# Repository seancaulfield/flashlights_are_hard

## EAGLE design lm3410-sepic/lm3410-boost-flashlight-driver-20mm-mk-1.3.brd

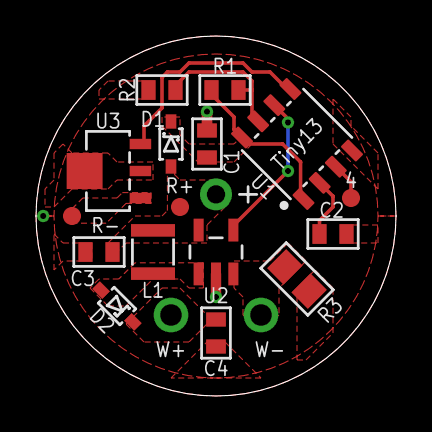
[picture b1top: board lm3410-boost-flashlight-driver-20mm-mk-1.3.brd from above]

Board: 2 copper layers, 20.0 x 20.0 mm, 21 parts (1 on the bottom side), 12 nets.

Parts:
4: M01SMD-1MM-DIA-NS; 1X01-SMD-1MM-DIA-NS
+: M01PTH-1MM-CIR-NS; 1X01-1MM-CIR-NS
-: M01NOT-A-VIA-NOPE; 1X01_NOSILK_NOSTOP
C1, C4: 10u; C0603-TIGHTER
C2: 1u; C0603-TIGHTER
C3: 4u7; C0603-TIGHTER
D1, D2: BAT165; SOD323-SCHOTTKY
FRAME1: FRAME-LETTERNO_PACKAGE; DUMMY
L1: 1uH; PFL2512
R1: 19K; R0603-TIGHTER
R2: 4K7; R0603-TIGHTER
R3: 0R127; R0805
R+: M01SMD-1MM-DIA-NS; 1X01-SMD-1MM-DIA-NS
R-: M01SMD-1MM-DIA-NS; 1X01-SMD-1MM-DIA-NS
U1: Tiny13; SO08-NARROWER
U2: LM3410XMF; SOT95P285X120-5N
U3: '7135; SOT89-NOTHERM
W+: M01PTH-1.2MM-NS; 1X01-1.2MM-NS
W-: M01PTH-1.2MM-NS; 1X01-1.2MM-NS

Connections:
4: 4.P$1, U1.3
GND: -.P$1, C1.2, C2.2, C3.2, C4.2, R2.1, R3.1, U1.4, U2.2, U3.4@1, U3.4@2
unnamed: C2.1, U1.2
PWM1: U1.6, U2.4
PWM2: U1.5, U3.3
R-: R-.P$1, U3.1
SW: D2.A, L1.P$2, U2.1
VBAT: +.1, C3.1, D1.A, L1.P$1, R+.P$1, U2.5
VCC: C1.1, D1.C, R1.2, U1.1, U1.8
VDIV: R1.1, R2.2, U1.7
WHITE+: C4.1, D2.C, W+.P$1
WHITE-: R3.2, U2.3, W-.P$1

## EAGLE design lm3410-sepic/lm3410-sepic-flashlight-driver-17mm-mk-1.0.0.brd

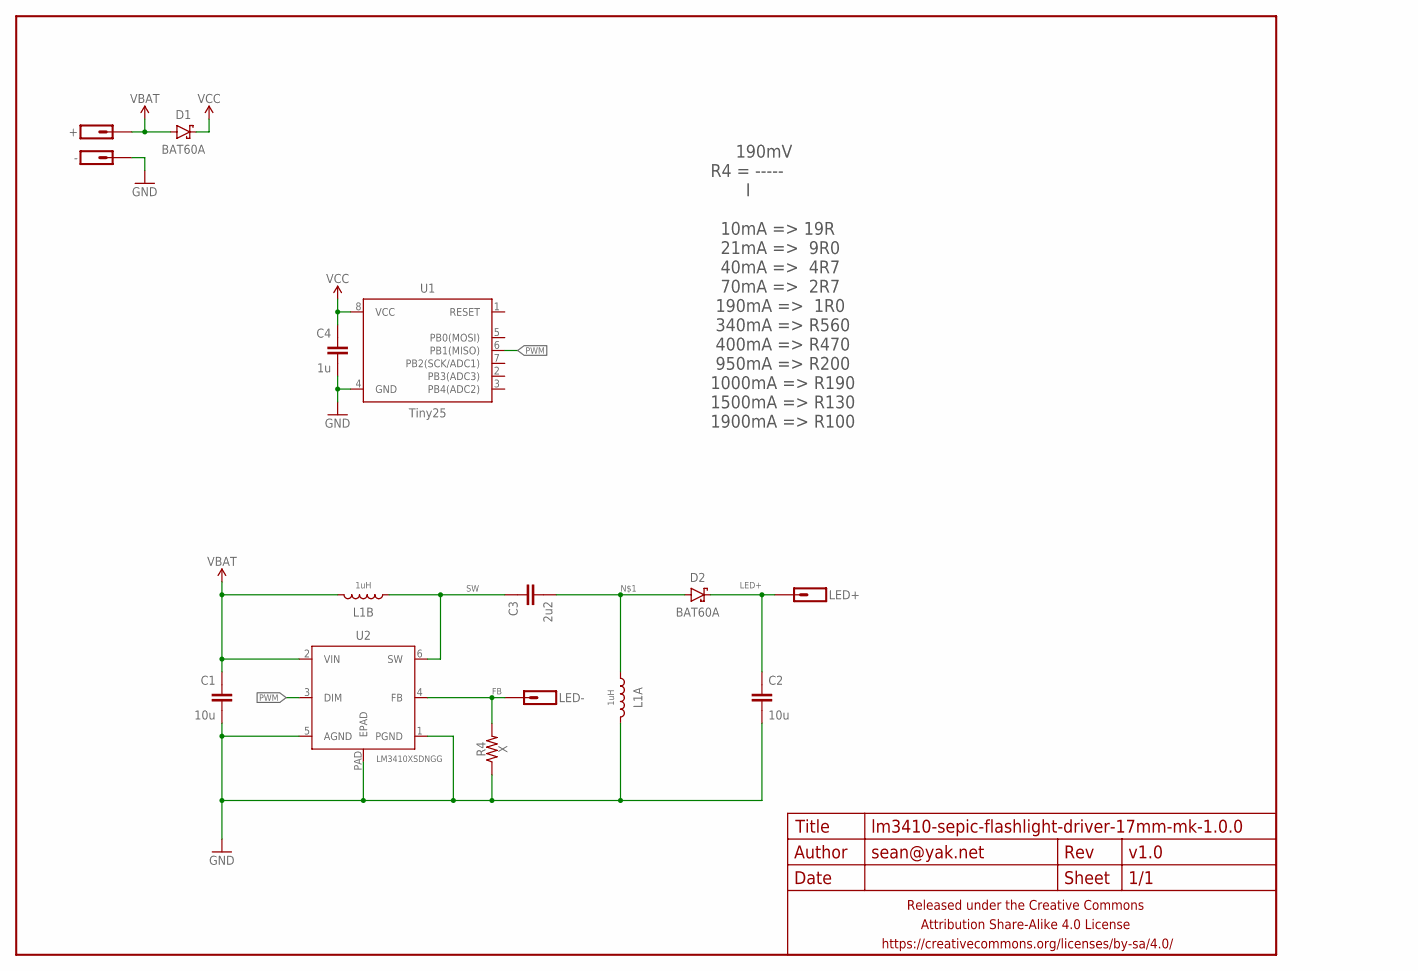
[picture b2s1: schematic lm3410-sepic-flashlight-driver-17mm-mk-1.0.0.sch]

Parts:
+: M01NOT-A-VIA-NOPE; 1X01_NOSILK_NOSTOP
-: M01NOT-A-VIA-NOPE; 1X01_NOSILK_NOSTOP
C1, C2: 10u; C0805-TIGHTER
C3: 2u2; C0603-TIGHTER
C4: 1u; C0603-TIGHTER
D1, D2: BAT60A; SOD323-SCHOTTKY
FRAME1: FRAME-LETTERNO_PACKAGE; DUMMY
L1: 1uH; LPD5030
LED+: M01PTH-1MM-CIR-NS; 1X01-1MM-CIR-NS
LED-: M01PTH-1MM-CIR-NS; 1X01-1MM-CIR-NS
R4: X; R0805-TIGHTER
U1: Tiny25; SO08-SKINNYPADS
U2: LM3410XSDNGG; DFN300X300X80-7N

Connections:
FB: LED-.1, R4.2, U2.4 (FB)
GND: -.P$1, C1.2, C2.2, C4.2, L1.2, R4.1, U1.4 (GND), U2.1 (PGND), U2.5 (AGND), U2.PAD (EPAD)
LED+: C2.1, D2.C, LED+.1
unnamed: C3.2, D2.A, L1.1
PWM: U1.6 (PB1(MISO)), U2.3 (DIM)
SW: C3.1, L1.4 (1), U2.6 (SW)
VBAT: +.P$1, C1.1, D1.A, L1.3 (2), U2.2 (VIN)
VCC: C4.1, D1.C, U1.8 (VCC)

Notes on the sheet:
190mV R4 = ----- I 10mA => 19R 21mA => 9R0 40mA => 4R7 70mA => 2R7 190mA => 1R0 340mA => R560 400mA => R470 950mA => R200 1000mA => R190 1500mA => R130 1900mA => R100

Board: 2 copper layers, 15 parts (1 on the bottom side), 8 nets, no tracks yet.

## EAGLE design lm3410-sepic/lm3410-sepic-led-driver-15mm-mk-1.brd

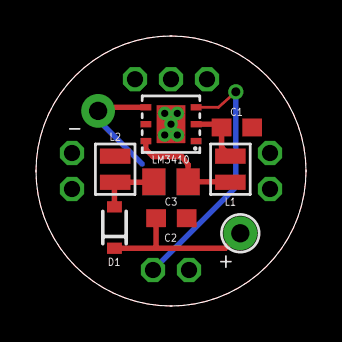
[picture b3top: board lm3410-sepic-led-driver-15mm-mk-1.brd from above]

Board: 2 copper layers, 15.0 x 15.0 mm, 14 parts (1 on the bottom side), 7 nets.

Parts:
+: M01PTH-KIT; 1X01-KIT
-: M01NOSILK-KIT; 1X01NS-KIT
C1, C2: 10uF; C0603
C3: 2.2uF; C0805
D1: BAT20J; SOD-323
JP1: 1X03-2MM-PTH
JP2, JP3, JP4: M02PTH-2MM; 1X02-2MM-PTH
L1, L2: 4.7uH; INDUCTOR_2X1.6MM
LM3410: LM3410XSD; DFN300X300X80-7N
R1: 0.68; R1206

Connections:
D0: JP3.P$1, LM3410.3
GND: C1.2, C2.2, JP1.P$1, JP1.P$3, L2.P$2, LM3410.1, LM3410.5, LM3410.7, LM3410.7@1, LM3410.7@2, LM3410.7@3, LM3410.7@4, LM3410.7@5, R1.1
LED_ANODE: +.1, C2.1, D1.C
unnamed: C3.2, D1.A, L2.P$1
unnamed: -.1, LM3410.4, R1.2
SW: C3.1, L1.P$2, LM3410.6
V_BATT+: C1.1, JP1.P$2, L1.P$1, LM3410.2

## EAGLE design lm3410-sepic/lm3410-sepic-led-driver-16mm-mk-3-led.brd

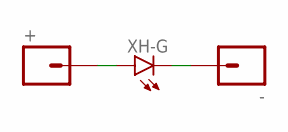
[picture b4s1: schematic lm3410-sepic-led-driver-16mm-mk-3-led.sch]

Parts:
+: M01PTH-1.2MM; 1X01-1.2MM
-: M01PTH-1.2MM-NS; 1X01-1.2MM-NS
XH-G: LEDBIG-ASS-RED-LED; LED-GULL-WINGS-MINE-MINE-MINE

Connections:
GND: -.P$1, XH-G.K (C), XH-G.K@1 (C), XH-G.K@3 (C), XH-G.K@4 (C), XH-G.K@5 (C), XH-G.K@7 (C), XH-G.K@8 (C), XH-G.K@9 (C), XH-G.K@10 (C), XH-G.K@11 (C), XH-G.K@12 (C), XH-G.K@13 (C), XH-G.K@14 (C), XH-G.K@15 (C), XH-G.K@16 (C), XH-G.K@17 (C), XH-G.K@18 (C), XH-G.K@19 (C), XH-G.K@20 (C), XH-G.K@21 (C), XH-G.K@23 (C), XH-G.K@24 (C), XH-G.K@25 (C)
VCC: +.P$1, XH-G.A

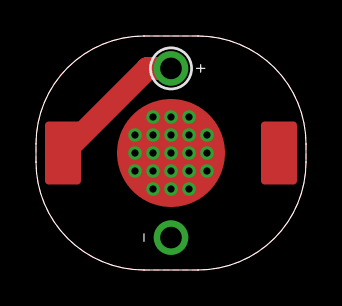
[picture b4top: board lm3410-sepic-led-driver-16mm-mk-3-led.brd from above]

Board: 2 copper layers, 15.0 x 13.0 mm, 3 parts (0 on the bottom side), 2 nets.

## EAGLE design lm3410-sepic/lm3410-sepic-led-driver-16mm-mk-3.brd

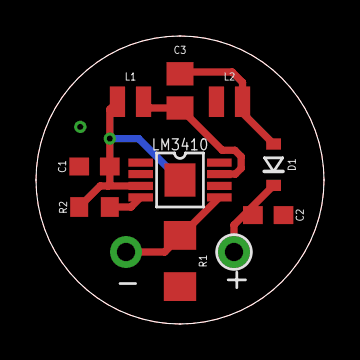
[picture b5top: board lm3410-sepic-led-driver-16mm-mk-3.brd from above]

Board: 2 copper layers, 16.0 x 16.0 mm, 13 parts (0 on the bottom side), 7 nets.

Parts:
+: M01PTH-KIT; 1X01-KIT
-: M01NOSILK-KIT; 1X01NS-KIT
C1, C2: 10uF; C0603
C3: 2.2uF; C0805
D1: BAT20J; SOD-323
JBATT+: M01NOT-A-VIA-NOPE; 1X01_NOSILK_NOSTOP
JBATT-: M01NOT-A-VIA-NOPE; 1X01_NOSILK_NOSTOP
L1, L2: 4.7uH; INDUCTOR_2X1.6MM
LM3410: LM3410XMYA; SOP65P490X110-9N-A
R1: 0.68; R1206
R2: 100k; R0603

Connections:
GND: C1.2, C2.2, JBATT-.P$1, L2.P$2, LM3410.2, LM3410.6, LM3410.9, R1.1
LED_ANODE: +.1, C2.1, D1.C
LED_CATHODE: -.1, LM3410.5, R1.2
unnamed: C3.2, D1.A, L2.P$1
unnamed: LM3410.4, R2.2
SW: C3.1, L1.P$2, LM3410.7
VCC: C1.1, JBATT+.P$1, L1.P$1, LM3410.3, R2.1

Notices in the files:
lm3410-sepic/lm3410-sepic-led-driver-16mm-mk-3.brd:
CC-BY-SA-4.0
parts and their libraries:
a_parts: Released under the Creative Commons Attribution Share-Alike 4.0 License
a_parts: https://creativecommons.org/licenses/by-sa/4.0
a_parts: Released under the Creative Commons
